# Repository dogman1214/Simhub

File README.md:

# Simhub
A custom-designed macropad design for my sim-racing use, and for general purpose as well.
This isn't physical at the moment, but rather a design you use to build your own macropad!

# Features:
* 3D - printed custom case
* 3 x 4 switch arrangement
* EC11 rotary encoder, with a switch built in
* USB-C connectivity
# CAD Model:

Everything is secured in place with 4 M3 screws and bolts, with the bolts serving a dual purpose as the base legs. The case is to be 3d-printed, along with the knob for the rotary encoder.

The render was made in Blender
The model was made in FreeCAD.

# PCB
This is the PCB, it was designed in KiCad.

Schematic 

PCB 

# Firmware
This hackpad uses QMK firmware for everything.
Since it was designed with video-game assistance in mind, you have to map all the keys in-game to use them.

*This keyboard has two modes.*

To swap between custom in-game keyboard usage and a normal numpad style keyboard, click down on the rotary encoder.

#Be aware: This Bill of Materials is what is expected to be bought & used. I haven't built the macropad yet.

### BOM:
This is eveyrthing you need to make this macropad:
* 12x Cherry MX Switches
* 12x DSA Keycaps
* 4x M3x16mm nuts and bolts
* 1x EC11 Rotary Encoder
* 1x XIAO RP2040
* 1x Case (3 printed parts)

# Bill of Materials - what you'll realistically buy

| Item Number              | Description                                                   | Quantity | Unit Price (USD) | Extended Price (USD) | Vendor                | Link |
|--------------------------|---------------------------------------------------------------|----------|------------------|----------------------|-----------------------|------|
| 4809-EC11E15204A3-ND     | EC11E15204A3 Alps Alpine ENCODER INCREM QUAD VERT PC PIN      | 1        | 4.41             | 4.41                 | Digi-Key              | https://www.digikey.com/en/products/detail/alps-alpine/EC11E15204A3/21721644 |
| 1597-102010428-ND        | 102010428 Seeed Technology Co., Ltd XIAO RP2040               | 1        | 4.88             | 4.88                 | Digi-Key              | https://www.digikey.com/en/products/detail/seeed-technology-co-ltd/102010428/14672129 |
| CHERRY MX2A RGB Brown Kit| 36 mechanical keyboard switches (tactile, no click)           | 1        | 19.99            | 19.99                | Amazon                | https://www.amazon.com/dp/B0FYR9Z777 |
| Fgruh 750PCS M3 Screws   | M3 hex socket bolts/nuts/washers set                          | 1        | 9.99             | 9.99                 | Amazon                | https://www.amazon.com/dp/B0FGV5FCBN |
| NeWear Relegendable Caps | DSA-style customizable transparent keycaps (12 pack)          | 1        | 12.50            | 12.50                | Amazon                | https://www.amazon.com/dp/B0DH91XV4T |
| Simhubb-PCBfiles_Y2      | PCB prototype Y2-13145810A, Green, 1.6mm, HASL (with lead)    | 5        | 0.40             | 2.00                 | JLCPCB                | (Generated from your Gerber ZIP; no product link) |
| Body.stl                 | 3D print PETG FDM, Standard finish, Translucent               | 1        | 5.40             | 5.40                 | Hudson Creative Group | (Custom print; no link) |
| Cover.stl                | 3D print PETG FDM, Standard finish, Translucent               | 1        | 5.40             | 5.40                 | Hudson Creative Group | (Custom print; no link) |
| Knob.stl                 | 3D print PETG FDM, Standard finish, Translucent               | 1        | 5.40             | 5.40                 | Hudson Creative Group | (Custom print; no link) |
 |

I hope you like this project/macropad!

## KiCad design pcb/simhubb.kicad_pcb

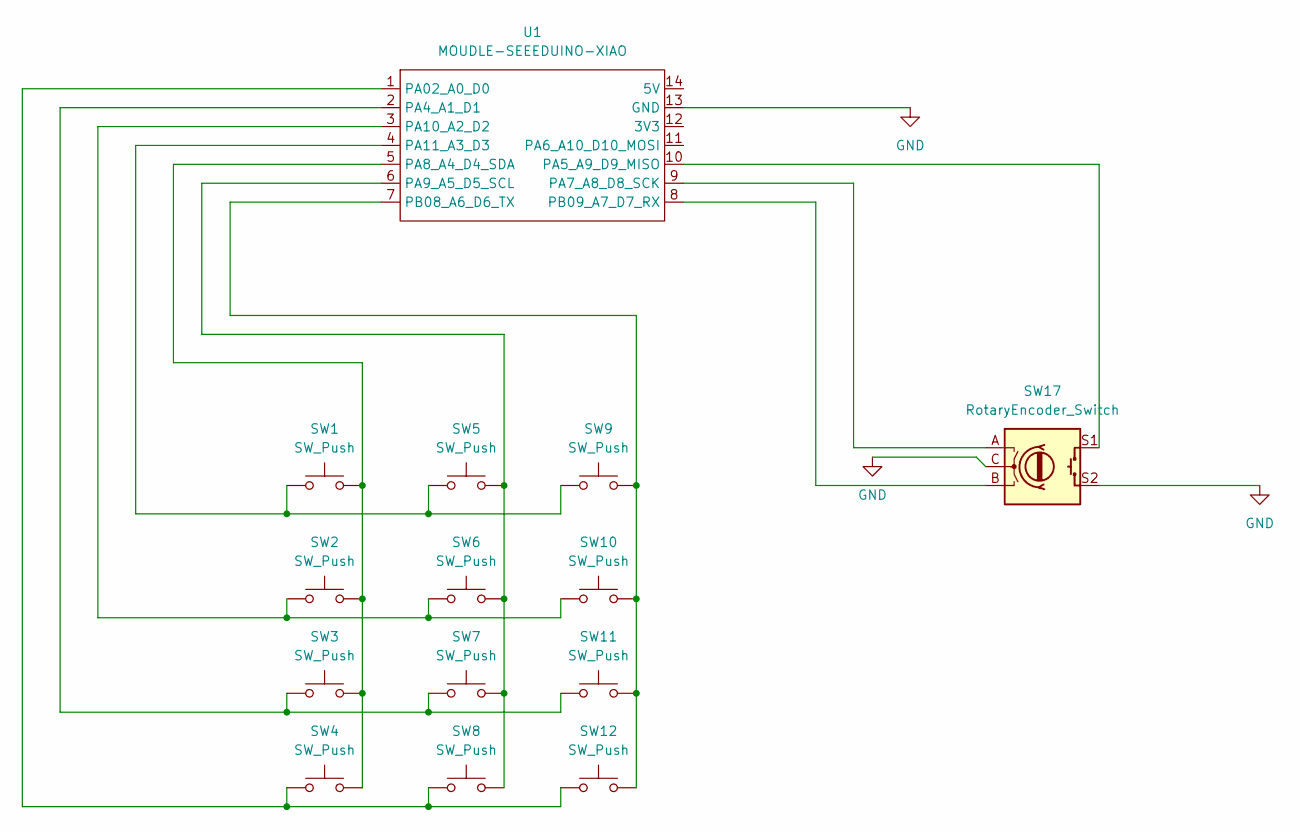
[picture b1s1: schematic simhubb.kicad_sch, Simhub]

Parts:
SW1, SW2, SW3, SW4, SW5, SW6, SW7, SW8, SW9, SW10, SW11, SW12: SW_Push; SW_Cherry_MX_1.00u_PCB
SW17: RotaryEncoder_Switch; RotaryEncoder_Alps_EC11E-Switch_Vertical_H20mm
U1: MOUDLE-SEEEDUINO-XIAO; XIAO-Generic-Hybrid-14P-2.54-21X17.8MM

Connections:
GND: SW17.C, SW17.S2, U1.13 (GND)
unnamed: SW4.1, SW8.1, SW12.1, U1.1 (PA02_A0_D0)
unnamed: SW3.1, SW7.1, SW11.1, U1.2 (PA4_A1_D1)
unnamed: SW17.S1, U1.10 (PA5_A9_D9_MISO)
unnamed: SW17.A, U1.9 (PA7_A8_D8_SCK)
unnamed: SW1.2, SW2.2, SW3.2, SW4.2, U1.5 (PA8_A4_D4_SDA)
unnamed: SW5.2, SW6.2, SW7.2, SW8.2, U1.6 (PA9_A5_D5_SCL)
unnamed: SW2.1, SW6.1, SW10.1, U1.3 (PA10_A2_D2)
unnamed: SW1.1, SW5.1, SW9.1, U1.4 (PA11_A3_D3)
unnamed: SW9.2, SW10.2, SW11.2, SW12.2, U1.7 (PB08_A6_D6_TX)
unnamed: SW17.B, U1.8 (PB09_A7_D7_RX)

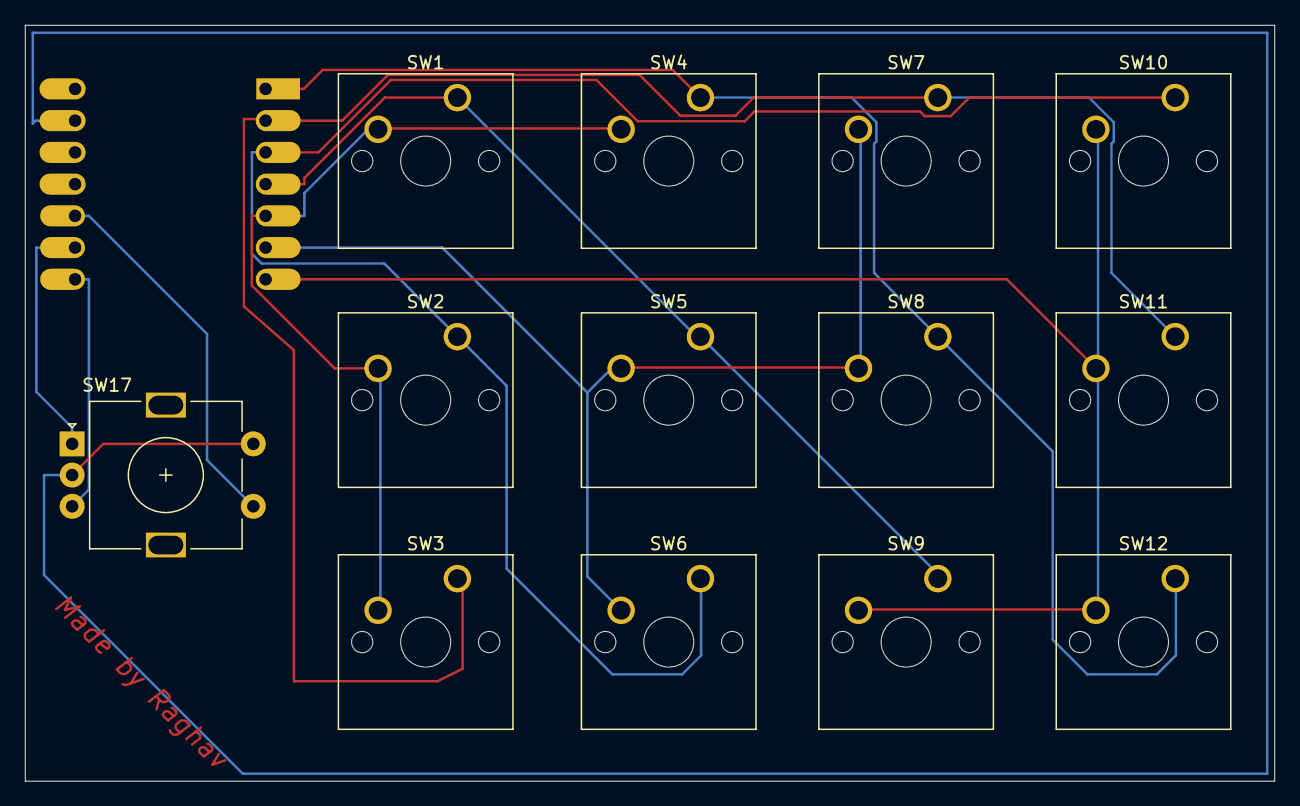
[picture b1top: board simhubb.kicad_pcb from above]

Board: 2 copper layers, 100.0 x 60.5 mm, 14 parts (1 on the bottom side), 11 nets.
